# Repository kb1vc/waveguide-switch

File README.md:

# Description:

This is an OpenSCAD model for a positioner using a model airplane
servo to control a WR90 waveguide switch.

There are four major components in the SCAD file, each may be
printed separately.

The base holds the servo, a magnet to "capture" the positioning
slug, and two mounts for optical sensors that signal proper alignment
and positioning of the slug.

The slug connects to the shaft of the waveguide switch.  The slug
has two "vanes" that hold small magnets to latch the assembly into
the transmit or receive position.

The cap covers and protects the positioner and associated control
electronics.

For optimal performance, add a stripe of white or copper paint to
the "outside" edge of the slug vanes to provide a strong positive
reflection when the slug is in position.

---------
Arduino sketch
---------

The arduino sketch is written for the module described in the "module"
subdirectory. It is based on the Sparkfun Aruino Pro Mini. 

# License:
See the LICENSE.txt file for copyright and conditions for re-use.

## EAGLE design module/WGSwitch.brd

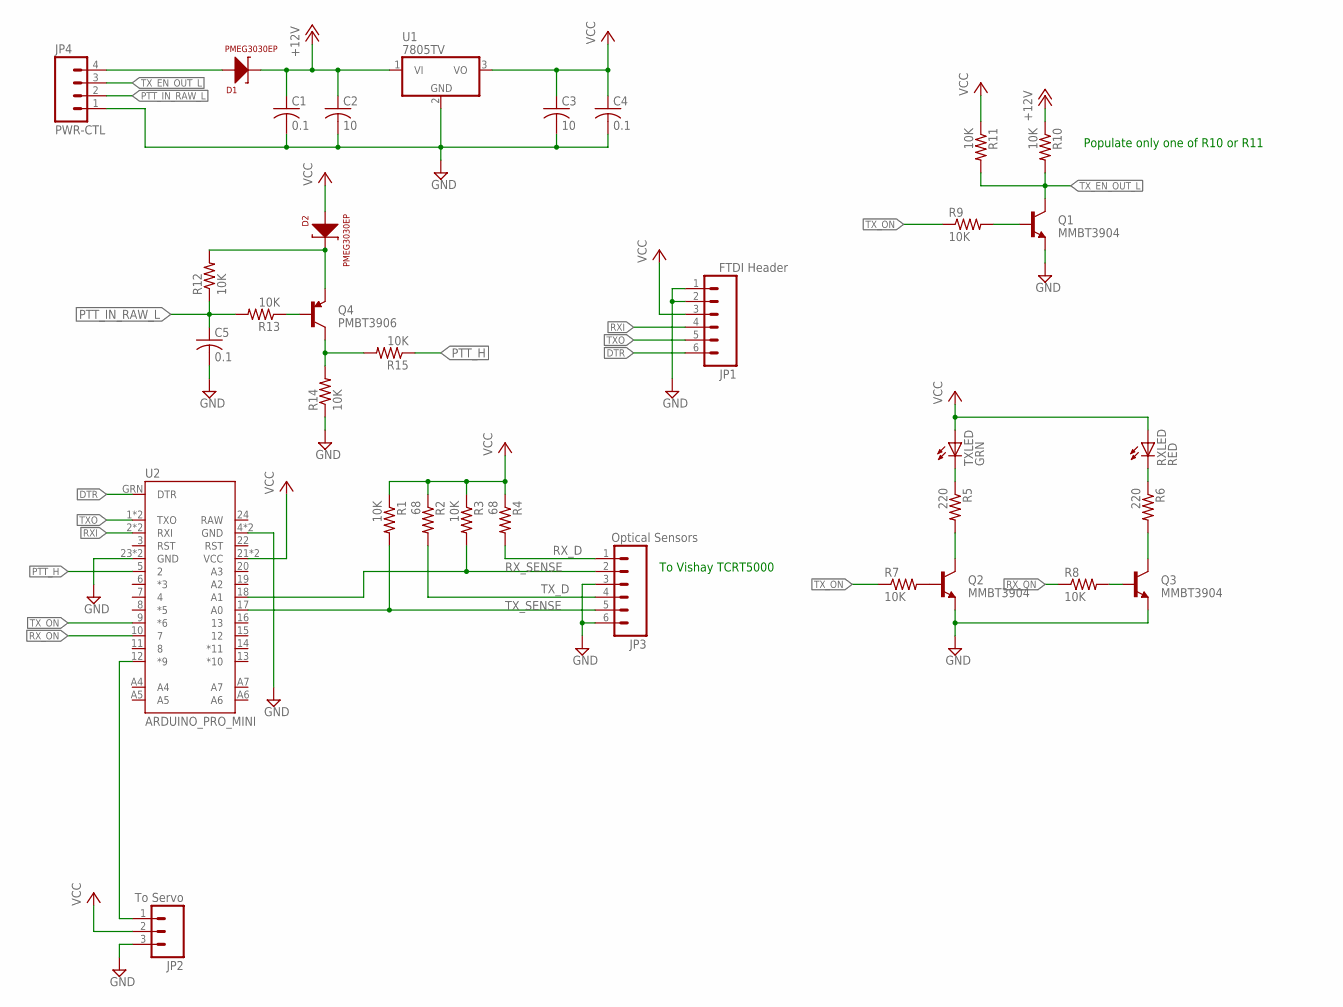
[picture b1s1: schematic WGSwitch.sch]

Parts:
C1, C4, C5: 0.1; C0805K
C2, C3: 10; C1206K
D1, D2: PMEG3030EP; SOD128
JP1: FTDI Header; 1X06
JP2: To Servo; 1X03
JP3: Optical Sensors; 1X06
JP4: PWR-CTL; 1X04
Q1, Q2, Q3: MMBT3904; SOT23-3
Q4: PMBT3906; SOT23-3
R1, R3, R7, R8, R9, R10, R11, R12, R13, R14, R15: 10K; R1206
R2, R4: 68; R1206
R5, R6: 220; R1206
RXLED: RED; LED5MM
TXLED: GRN; LED5MM
U1: 7805TV; TO220V
U2: ARDUINO_PRO_MINI

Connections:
+12V: C1.1, C2.1, D1.P$2 (C), R10.1, U1.1 (VI)
DTR: JP1.6, U2.GRN (DTR)
GND: C1.2, C2.2, C3.2, C4.2, C5.2, JP1.1, JP1.2, JP2.3, JP3.3, JP3.6, JP4.1, Q1.2 (E), Q2.2 (E), Q3.2 (E), R14.1, U1.2 (GND), U2.4 (GND), U2.23 (GND), U2.BLK (GND), U2.GND
unnamed: JP2.1, U2.12 (*9)
unnamed: Q1.1 (B), R9.2
unnamed: Q2.1 (B), R7.2
unnamed: R6.1, RXLED.K (C)
unnamed: D2.P$2 (C), Q4.2 (E), R12.2
unnamed: Q2.3 (C), R5.2
unnamed: Q3.3 (C), R6.2
unnamed: Q3.1 (B), R8.2
unnamed: Q4.1 (B), R13.1
unnamed: D1.P$1 (A), JP4.4
unnamed: Q4.3 (C), R14.2, R15.2
PTT_H: R15.1, U2.5 (2)
PTT_IN_RAW_L: C5.1, JP4.2, R12.1, R13.2
RXI: JP1.4, U2.2 (RXI), U2.RXI
RX_D: JP3.1, R4.2
RX_ON: R8.1, U2.10 (7)
RX_SENSE: JP3.2, R3.2, U2.18 (A1)
TXO: JP1.5, U2.1 (TXO), U2.TXO
TX_D: JP3.4, R2.2
TX_EN_OUT_L: JP4.3, Q1.3 (C), R10.2, R11.2
TX_LED: R5.1, TXLED.K (C)
TX_ON: R7.1, R9.1, U2.9 (*6)
TX_SENSE: JP3.5, R1.2, U2.17 (A0)
VCC: C3.1, C4.1, D2.P$1 (A), JP1.3, JP2.2, R1.1, R2.1, R3.1, R4.1, R11.1, RXLED.A, TXLED.A, U1.3 (VO), U2.21 (VCC), U2.VCC

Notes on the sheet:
To Vishay TCRT5000
Populate only one of R10 or R11

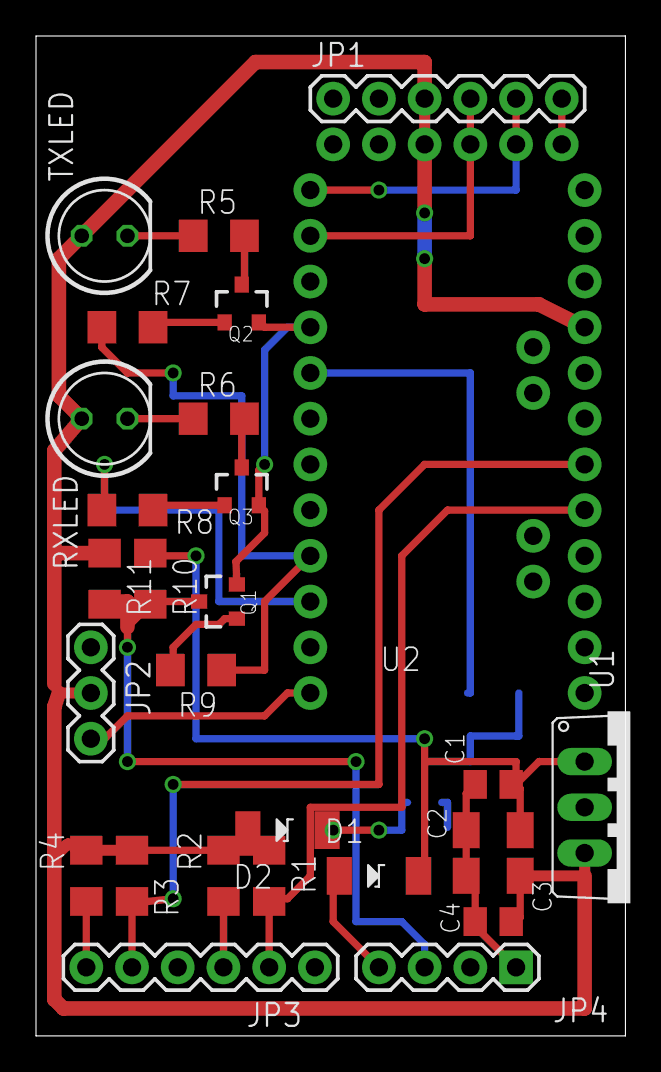
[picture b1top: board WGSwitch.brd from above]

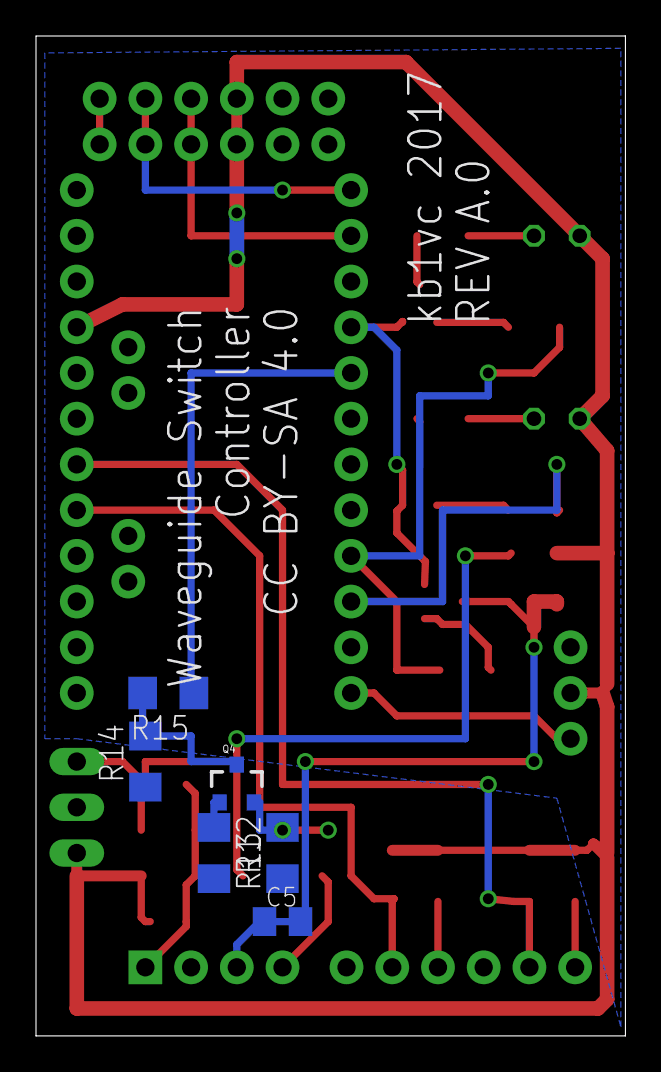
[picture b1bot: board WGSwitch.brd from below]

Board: 2 copper layers, 32.7 x 55.5 mm, 34 parts (6 on the bottom side), 27 nets.

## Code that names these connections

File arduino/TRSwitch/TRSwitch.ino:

/* Sweep
 by BARRAGAN <http://barraganstudio.com> 
 This example code is in the public domain.

 modified 8 Nov 2013
 by Scott Fitzgerald
 http://arduino.cc/en/Tutorial/Sweep
*/ 

#include <Servo.h> 
 
 
Servo myservo;  // create servo object to control a servo 
                // twelve servo objects can be created on most boards
 
int RX_pos = 0;
int RX_rest_pos = 45;
int TX_pos = 175;
int TX_rest_pos = 135;
int Center = 90;
int actuator_delay = 750; // in mS

#define SERVO_PIN 9
#define SENSE_PIN 2
#define OUT_PIN 3
#define RX_LED 7
#define TX_LED 6
#define RX_Sense A1
#define TX_Sense A0

#define RX_Threshold 250
#define TX_Threshold 250

void setup() 
{ 
  myservo.attach(SERVO_PIN);  // attaches the servo on pin 9 to the servo object 
  pinMode(SENSE_PIN, INPUT_PULLUP);
  pinMode(OUT_PIN, OUTPUT);
  pinMode(RX_LED, OUTPUT);
  pinMode(TX_LED, OUTPUT);
  delay(500);
  setMode(1);
  
  Serial.begin(19200);
  while(!Serial); 
  
} 

void readSensors()
{
  int rxs = analogRead(RX_Sense);
  int txs = analogRead(TX_Sense);
  int rxs2 = analogRead(RX_Sense);
  int txs2 = analogRead(TX_Sense);
  Serial.print("RXS "); 
  Serial.print(rxs); Serial.print(' ');
  Serial.print(rxs2);
  Serial.print("   TXS "); 
  Serial.print(txs); Serial.print(' ');
  Serial.println(txs2);  
}

// return 1 for RX -1 for TX and 0 for no dice
int checkSensors()
{
  int rxs = analogRead(RX_Sense);
  int txs = analogRead(TX_Sense);
  
  if((rxs < RX_Threshold) && (txs > TX_Threshold)) 
    return 1;
  else if((rxs > RX_Threshold) && (txs < TX_Threshold))
    return -1;
  else {
    Serial.print("! rxs txs = ");
    Serial.print(rxs); Serial.print("  "); Serial.println(txs);
    return 0;
  }
}


void setLEDs(int rx_mode)
{
  if(rx_mode) {
    digitalWrite(RX_LED, HIGH);
    digitalWrite(TX_LED, LOW);
  }
  else {
    digitalWrite(RX_LED, LOW);
    digitalWrite(TX_LED, HIGH);
  }
}

 
void setMode(int rx_mode) {
  int flag = 1; 
  if(rx_mode) {
    while(flag) {
      myservo.write(RX_pos);
      delay(actuator_delay);
      checkSensors();  // read twice to spin up A/D converter
      if(checkSensors() == 1) flag = 0;
    }
    myservo.write(RX_rest_pos);
  }
  else {
   while(flag) {
      myservo.write(TX_pos);
      checkSensors(); // read twice to spin up A/D converter
      if(checkSensors() == -1) flag = 0;
      else delay(actuator_delay);
    }
    myservo.write(TX_rest_pos);   
  }
  setLEDs(rx_mode);
  
  //readSensors();
}

void setPos(int pos, int rest_pos) {
  myservo.write(pos);
  delay(actuator_delay);
  myservo.write(rest_pos);
}

int last_sense = 1; 

void loop() 
{ 
  int new_sense  = digitalRead(SENSE_PIN);
  
  if(new_sense == last_sense) {
    // nothing has happened. 
    delay(100);
    readSensors();
  }
  else if(new_sense) {
    setMode(1);
  }
  else {
    setMode(0);
  }
  last_sense = new_sense; 

} 

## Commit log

2017-01-19 Almost there.
2017-01-21 New trial -- reduce slug height
2017-01-21 Final proto?
2017-01-28 Made cover... adjusted base.
2017-02-20 Added controller sketch, and new PC module.
2017-02-21 Added optical sensors. Trimmed slug to fit them.
2017-02-21 added text to readme
2017-02-22 Added hole and tabs for connector mount
2017-02-23 Added mount for connector.
2017-02-23 added article source
2017-02-23 added picture of trial and error.
2017-03-05 update sketch to work with full module.
2017-03-11 Added Sleep Mode version
2017-03-11 Bumped IR sensor thresholds to handle dark envelope.
2017-03-11 cleanup and optimize TRSwitchSleep to eliminate extra delay.
2017-03-15 more progress -- added images
2017-03-15 more progress
2017-03-18 Just about right.
2017-03-18 Got the spacing right, it seems
2017-03-18 First draft done.
2017-03-20 Ready for the proceedings?
2017-03-21 missing file -- added it.
2017-04-15 Saving the module... this will be rev B.
2017-04-15 Rev C of module -- fixed diode footprints.

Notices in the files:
module/WGSwitch.brd:
CC BY-SA 4.0
parts and their libraries:
SparkFun-Connectors: Licensing: Creative Commons ShareAlike 4.0 International - https://creativecommons.org/licenses/by-sa/4.0
